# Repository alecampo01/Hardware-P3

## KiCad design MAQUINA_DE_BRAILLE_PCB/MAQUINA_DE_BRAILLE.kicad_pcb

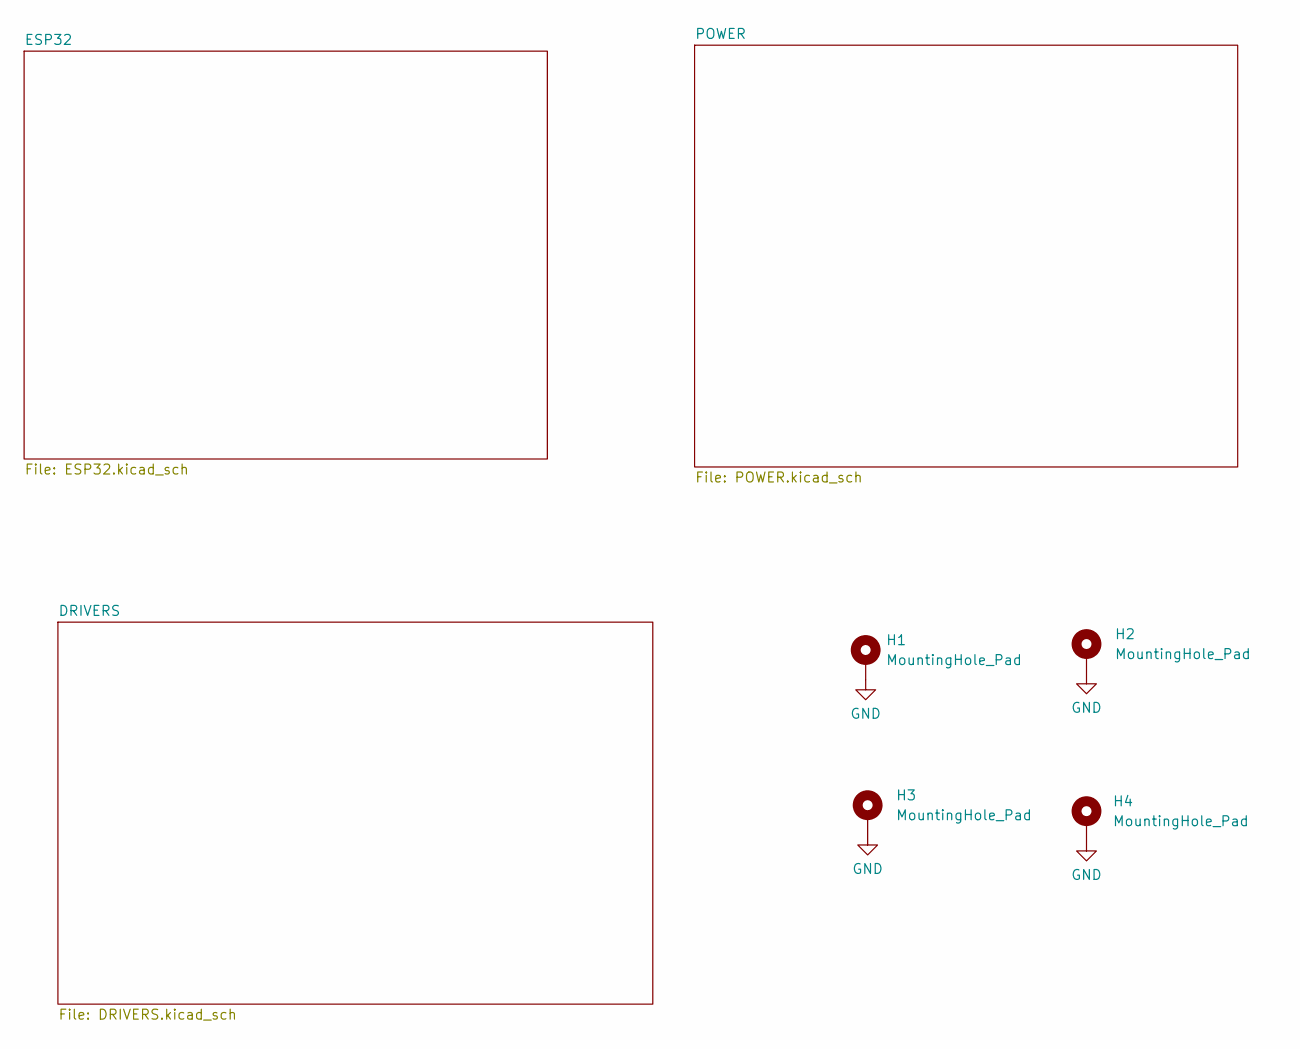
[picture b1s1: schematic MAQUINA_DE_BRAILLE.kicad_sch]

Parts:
H1, H2, H3, H4: MountingHole_Pad; MountingHole_3mm_Pad_Via

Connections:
GND: H1.1, H2.1, H3.1, H4.1; also elsewhere on the board

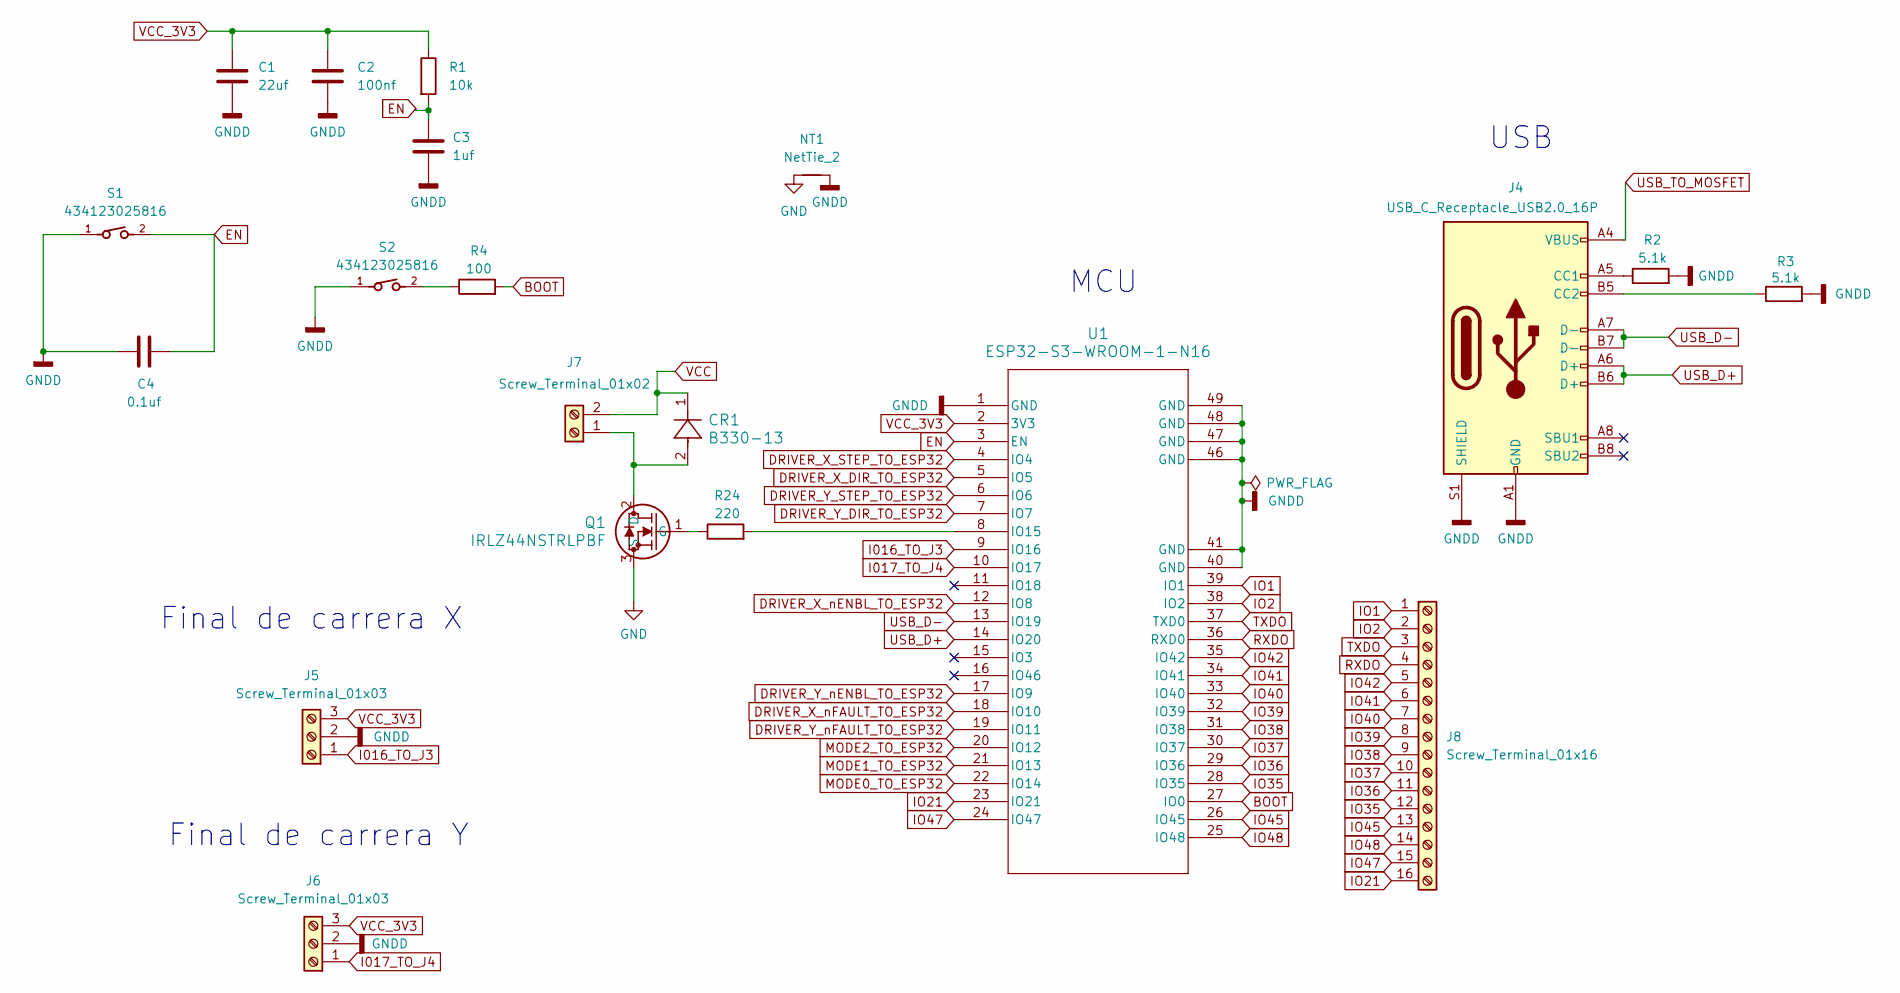
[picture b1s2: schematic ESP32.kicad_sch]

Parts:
C1: 22uf; C_0805_2012Metric_Pad1.18x1.45mm_HandSolder
C2: 100nf; C_0805_2012Metric_Pad1.18x1.45mm_HandSolder
C3: 1uf; C_0805_2012Metric_Pad1.18x1.45mm_HandSolder
C4: 0.1uf; C_0805_2012Metric_Pad1.18x1.45mm_HandSolder
CR1: B330-13; SMC_DIO
J4: USB_C_Receptacle_USB2.0_16P; USB_C_Receptacle_GCT_USB4105-xx-A_16P_TopMnt_Horizontal
J5, J6: Screw_Terminal_01x03; TerminalBlock_Xinya_XY308-2.54-3P_1x03_P2.54mm_Horizontal
J7: Screw_Terminal_01x02; TerminalBlock_Phoenix_MKDS-3-2-5.08_1x02_P5.08mm_Horizontal
J8: Screw_Terminal_01x16; TerminalBlock_Xinya_XY308-2.54-16P_1x16_P2.54mm_Horizontal
NT1: NetTie_2; NetTie-2_SMD_Pad2.0mm
Q1: IRLZ44NSTRLPBF; NMOSGDS_D2PAK_INF
R1: 10k; R_0805_2012Metric_Pad1.20x1.40mm_HandSolder
R2, R3: 5.1k; R_0805_2012Metric_Pad1.20x1.40mm_HandSolder
R4: 100; R_0805_2012Metric_Pad1.20x1.40mm_HandSolder
R24: 220; R_0805_2012Metric_Pad1.20x1.40mm_HandSolder
S1, S2: 434123025816
U1: ESP32-S3-WROOM-1-N16; ESP32-S3-WROOM-1_EXP

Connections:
BOOT: R4.2, U1.27 (IO0)
DRIVER_X_DIR_TO_ESP32: U1.5 (IO5); also elsewhere on the board
DRIVER_X_STEP_TO_ESP32: U1.4 (IO4); also elsewhere on the board
DRIVER_X_nENBL_TO_ESP32: U1.12 (IO8); also elsewhere on the board
DRIVER_X_nFAULT_TO_ESP32: U1.18 (IO10); also elsewhere on the board
DRIVER_Y_DIR_TO_ESP32: U1.7 (IO7); also elsewhere on the board
DRIVER_Y_STEP_TO_ESP32: U1.6 (IO6); also elsewhere on the board
DRIVER_Y_nENBL_TO_ESP32: U1.17 (IO9); also elsewhere on the board
DRIVER_Y_nFAULT_TO_ESP32: U1.19 (IO11); also elsewhere on the board
EN: C3.1, C4.2, R1.2, S1.2, U1.3 (EN); also elsewhere on the board
GND: NT1.1, Q1.3 (S); also elsewhere on the board
GNDD: C1.2, C2.2, C3.2, C4.1, J4.A1 (GND), J4.A12 (GND), J4.B1 (GND), J4.B12 (GND), J4.S1 (SHIELD), J5.2, J6.2, NT1.2, R2.2, R3.2, S1.1, S2.1, U1.1 (GND), U1.40 (GND), U1.41 (GND), U1.42, U1.43, U1.44, U1.45, U1.46 (GND), U1.47 (GND), U1.48 (GND), U1.49 (GND); also elsewhere on the board
I016_TO_J3: J5.1, U1.9 (IO16)
I017_TO_J4: J6.1, U1.10 (IO17)
IO1: J8.1, U1.39 (IO1)
IO2: J8.2, U1.38 (IO2)
IO21: J8.16, U1.23 (IO21)
IO35: J8.12, U1.28 (IO35)
IO36: J8.11, U1.29 (IO36)
IO37: J8.10, U1.30 (IO37)
IO38: J8.9, U1.31 (IO38)
IO39: J8.8, U1.32 (IO39)
IO40: J8.7, U1.33 (IO40)
IO41: J8.6, U1.34 (IO41)
IO42: J8.5, U1.35 (IO42)
IO45: J8.13, U1.26 (IO45)
IO47: J8.15, U1.24 (IO47)
IO48: J8.14, U1.25 (IO48)
MODE0_TO_ESP32: U1.22 (IO14); also elsewhere on the board
MODE1_TO_ESP32: U1.21 (IO13); also elsewhere on the board
MODE2_TO_ESP32: U1.20 (IO12); also elsewhere on the board
unnamed: J4.A5 (CC1), R2.1
unnamed: J4.B5 (CC2), R3.1
unnamed: CR1.2, J7.1, Q1.2 (D)
unnamed: Q1.1 (G), R24.1
unnamed 51: R4.1, S2.2; also elsewhere on the board
unnamed: R24.2, U1.8 (IO15)
RXDO: J8.4, U1.36 (RXD0)
TXDO: J8.3, U1.37 (TXD0)
USB_D+: J4.A6 (D+), J4.B6 (D+), U1.14 (IO20)
USB_D-: J4.A7 (D-), J4.B7 (D-), U1.13 (IO19)
USB_TO_MOSFET: J4.A4 (VBUS), J4.A9 (VBUS), J4.B4 (VBUS), J4.B9 (VBUS); also elsewhere on the board
VCC: CR1.1, J7.2; also elsewhere on the board
VCC_3V3: C1.1, C2.1, J5.3, J6.3, R1.1, U1.2 (3V3); also elsewhere on the board

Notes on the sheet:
USB
MCU
Final de carrera Y
Final de carrera X

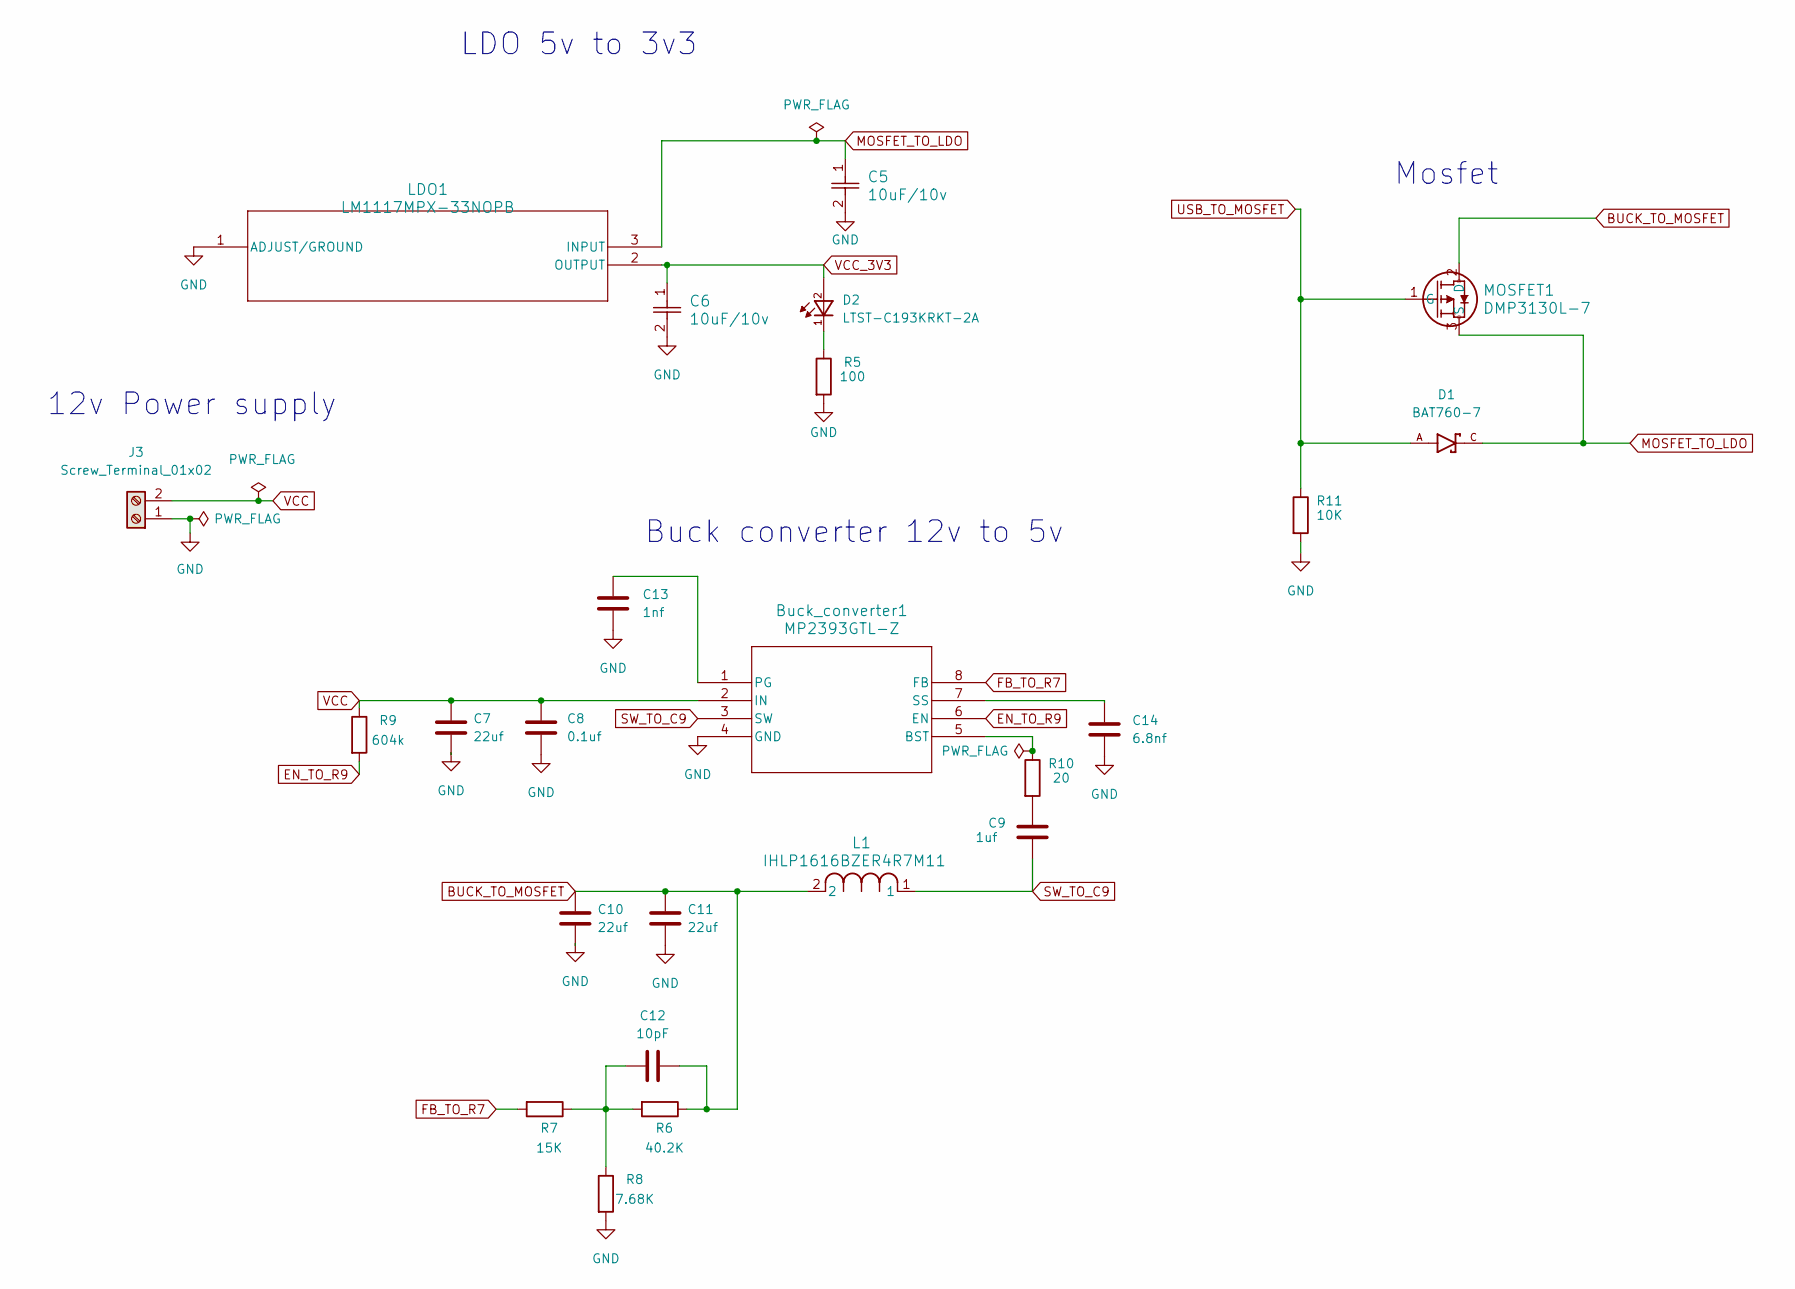
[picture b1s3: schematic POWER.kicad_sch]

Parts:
Buck_converter1: MP2393GTL-Z; SOT583_MP2393
C5, C6: 10uF/10v; CAP_293D_B_VIS
C7, C10, C11: 22uf; C_0805_2012Metric_Pad1.18x1.45mm_HandSolder
C8: 0.1uf; C_0805_2012Metric_Pad1.18x1.45mm_HandSolder
C9: 1uf; C_0805_2012Metric_Pad1.18x1.45mm_HandSolder
C12: 10pF; C_0805_2012Metric_Pad1.18x1.45mm_HandSolder
C13: 1nf; C_0805_2012Metric_Pad1.18x1.45mm_HandSolder
C14: 6.8nf; C_0805_2012Metric_Pad1.18x1.45mm_HandSolder
D1: BAT760-7; SOD2513X120N; PARTREV 9-2
D2: LTST-C193KRKT-2A; 0603
J3: Screw_Terminal_01x02; TerminalBlock_Phoenix_MKDS-3-2-5.08_1x02_P5.08mm_Horizontal
L1: IHLP1616BZER4R7M11; IND_IHLP-1616BZ_VIS
LDO1: LM1117MPX-33NOPB; SOT223-318H_OSI
MOSFET1: DMP3130L-7; SOT-23_DMP3130L_DIO
R5: 100; R_0805_2012Metric_Pad1.20x1.40mm_HandSolder
R6: 40.2K; R_0805_2012Metric_Pad1.20x1.40mm_HandSolder
R7: 15K; R_0805_2012Metric_Pad1.20x1.40mm_HandSolder
R8: 7.68K; R_0805_2012Metric_Pad1.20x1.40mm_HandSolder
R9: 604k; R_0805_2012Metric_Pad1.20x1.40mm_HandSolder
R10: 20; R_0805_2012Metric_Pad1.20x1.40mm_HandSolder
R11: 10K; R_0805_2012Metric_Pad1.20x1.40mm_HandSolder

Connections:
EN_TO_R9: Buck_converter1.6 (EN), R9.2
FB_TO_R7: Buck_converter1.8 (FB), R7.2
GND: Buck_converter1.4 (GND), C5.2, C6.2, C7.2, C8.2, C10.2, C11.2, C13.2, C14.2, J3.1, LDO1.1 (ADJUST/GROUND), R5.2, R8.2, R11.2; also elsewhere on the board
unnamed: Buck_converter1.5 (BST), R10.1
unnamed: Buck_converter1.1 (PG), C13.1
unnamed: Buck_converter1.7 (SS), C14.1
unnamed: C9.1, R10.2
unnamed: C12.1, R6.2, R7.1, R8.1
unnamed: D2.1, R5.1
SW_TO_C9: Buck_converter1.3 (SW), C9.2, L1.1
USB_TO_MOSFET: D1.A, MOSFET1.1 (G), R11.1; also elsewhere on the board
VCC: Buck_converter1.2 (IN), C7.1, C8.1, J3.2, R9.1; also elsewhere on the board
VCC_3V3: C6.1, D2.2, LDO1.2 (OUTPUT); also elsewhere on the board

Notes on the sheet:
Buck converter 12v to 5v
Mosfet
12v Power supply
LDO 5v to 3v3

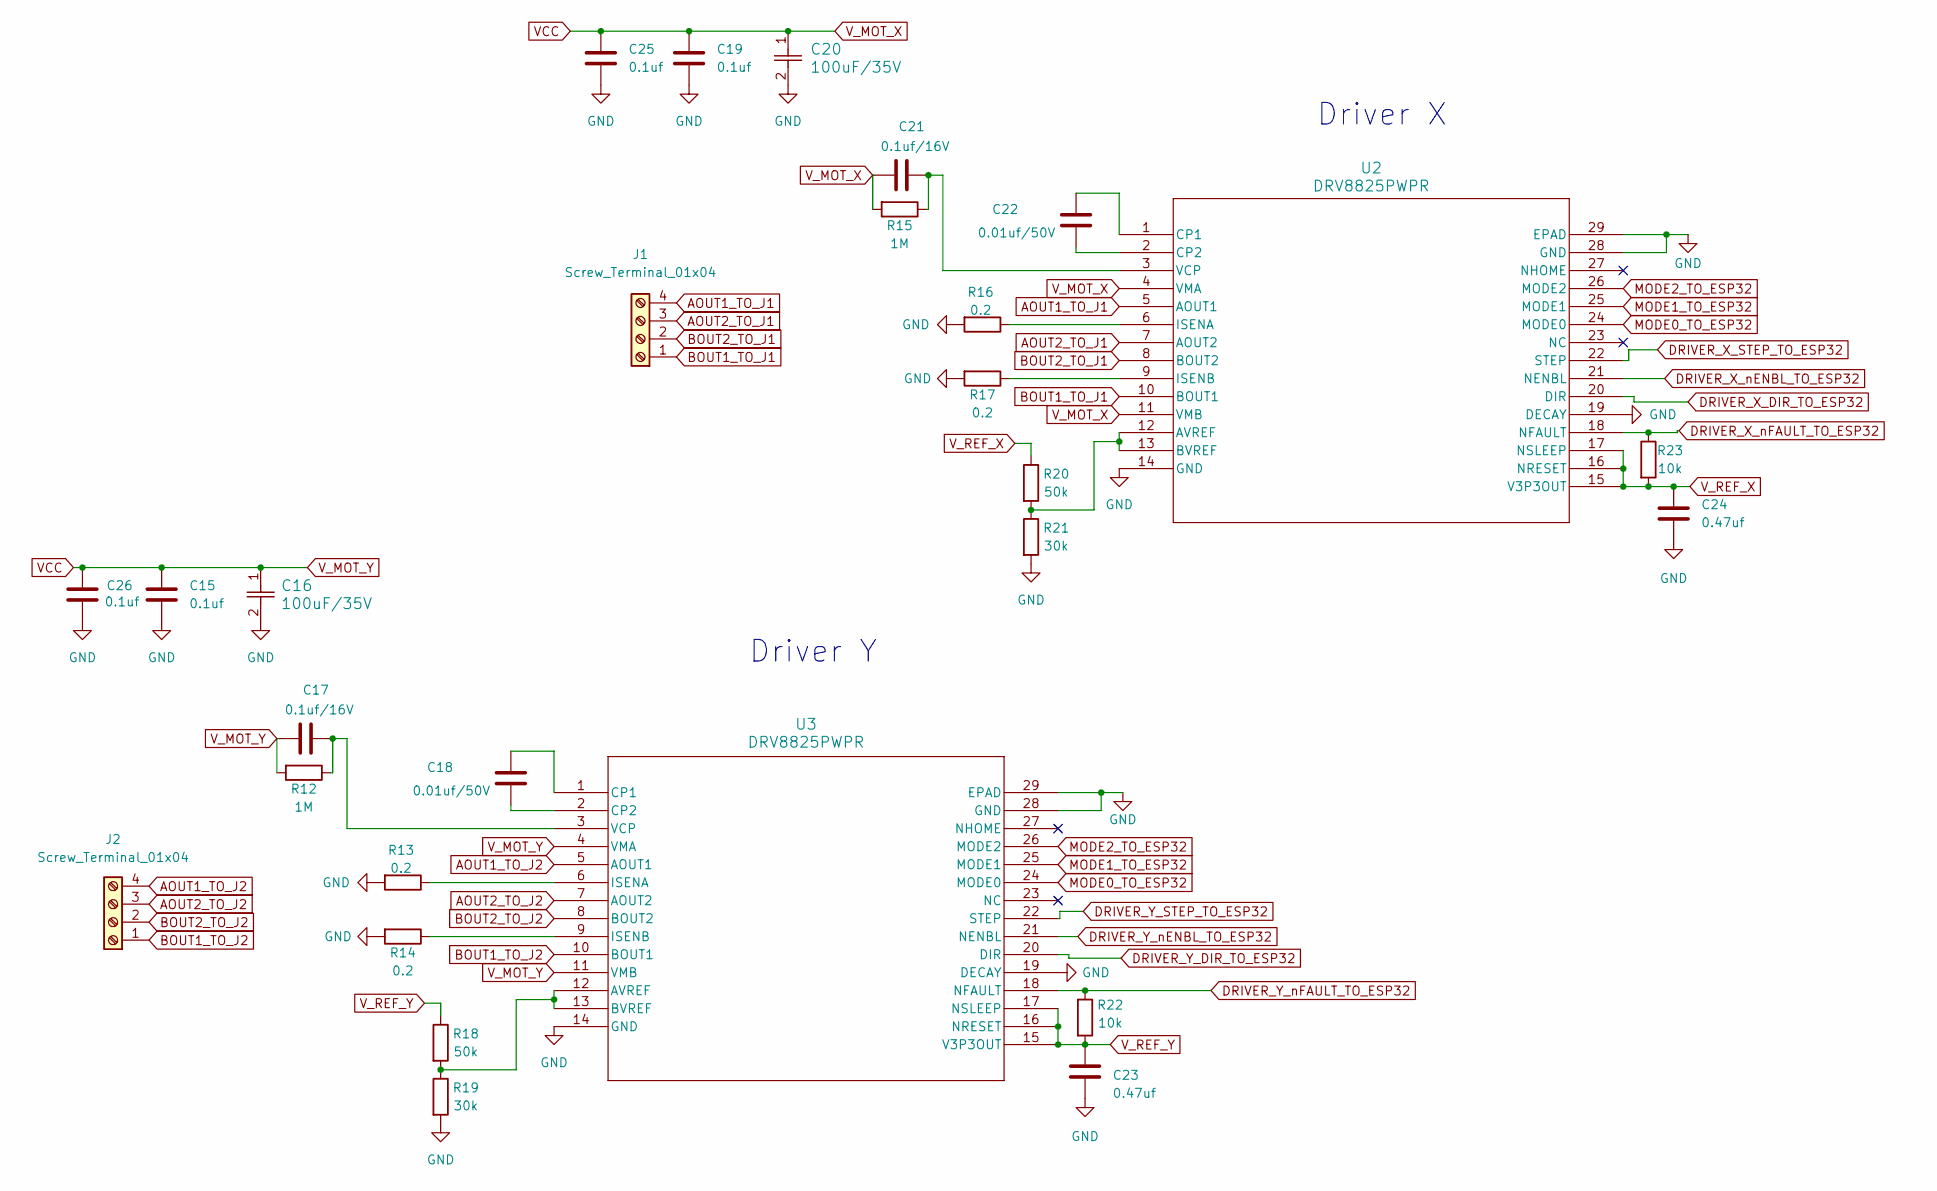
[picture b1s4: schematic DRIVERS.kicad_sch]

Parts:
C15, C19, C25, C26: 0.1uf; C_0805_2012Metric_Pad1.18x1.45mm_HandSolder
C16, C20: 100uF/35V; CAP_WCAP-ASLI_06p3X07p7_WRE
C17, C21: 0.1uf/16V; C_0805_2012Metric_Pad1.18x1.45mm_HandSolder
C18, C22: 0.01uf/50V; C_0805_2012Metric_Pad1.18x1.45mm_HandSolder
C23, C24: 0.47uf; C_0805_2012Metric_Pad1.18x1.45mm_HandSolder
J1, J2: Screw_Terminal_01x04; TerminalBlock_Xinya_XY308-2.54-4P_1x04_P2.54mm_Horizontal
R12, R15: 1M; R_0805_2012Metric_Pad1.20x1.40mm_HandSolder
R13, R14, R16, R17: 0.2; R_0805_2012Metric_Pad1.20x1.40mm_HandSolder
R18, R20: 50k; R_0805_2012Metric_Pad1.20x1.40mm_HandSolder
R19, R21: 30k; R_0805_2012Metric_Pad1.20x1.40mm_HandSolder
R22, R23: 10k; R_0805_2012Metric_Pad1.20x1.40mm_HandSolder
U2, U3: DRV8825PWPR; PWP28_5P18X3P1

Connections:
AOUT1_TO_J1: J1.4, U2.5 (AOUT1)
AOUT1_TO_J2: J2.4, U3.5 (AOUT1)
AOUT2_TO_J1: J1.3, U2.7 (AOUT2)
AOUT2_TO_J2: J2.3, U3.7 (AOUT2)
BOUT1_TO_J1: J1.1, U2.10 (BOUT1)
BOUT1_TO_J2: J2.1, U3.10 (BOUT1)
BOUT2_TO_J1: J1.2, U2.8 (BOUT2)
BOUT2_TO_J2: J2.2, U3.8 (BOUT2)
DRIVER_X_DIR_TO_ESP32: U2.20 (DIR); also elsewhere on the board
DRIVER_X_STEP_TO_ESP32: U2.22 (STEP); also elsewhere on the board
DRIVER_X_nENBL_TO_ESP32: U2.21 (NENBL); also elsewhere on the board
DRIVER_X_nFAULT_TO_ESP32: R23.1, U2.18 (NFAULT); also elsewhere on the board
DRIVER_Y_DIR_TO_ESP32: U3.20 (DIR); also elsewhere on the board
DRIVER_Y_STEP_TO_ESP32: U3.22 (STEP); also elsewhere on the board
DRIVER_Y_nENBL_TO_ESP32: U3.21 (NENBL); also elsewhere on the board
DRIVER_Y_nFAULT_TO_ESP32: R22.1, U3.18 (NFAULT); also elsewhere on the board
GND: C15.2, C16.2, C19.2, C20.2, C23.2, C24.2, C25.2, C26.2, R13.2, R14.2, R16.2, R17.2, R19.2, R21.2, U2.14 (GND), U2.19 (DECAY), U2.28 (GND), U2.29 (EPAD), U3.14 (GND), U3.19 (DECAY), U3.28 (GND), U3.29 (EPAD); also elsewhere on the board
MODE0_TO_ESP32: U2.24 (MODE0), U3.24 (MODE0); also elsewhere on the board
MODE1_TO_ESP32: U2.25 (MODE1), U3.25 (MODE1); also elsewhere on the board
MODE2_TO_ESP32: U2.26 (MODE2), U3.26 (MODE2); also elsewhere on the board
unnamed: R20.2, R21.1, U2.12 (AVREF), U2.13 (BVREF)
unnamed: C22.1, U2.1 (CP1)
unnamed: C22.2, U2.2 (CP2)
unnamed: R16.1, U2.6 (ISENA)
unnamed: R17.1, U2.9 (ISENB)
unnamed: C21.1, R15.1, U2.3 (VCP)
unnamed: R18.2, R19.1, U3.12 (AVREF), U3.13 (BVREF)
unnamed: C18.1, U3.1 (CP1)
unnamed: C18.2, U3.2 (CP2)
unnamed: R13.1, U3.6 (ISENA)
unnamed: R14.1, U3.9 (ISENB)
unnamed: C17.1, R12.1, U3.3 (VCP)
VCC: C15.1, C16.1, C17.2, C19.1, C20.1, C21.2, C25.1, C26.1, R12.2, R15.2, U2.4 (VMA), U2.11 (VMB), U3.4 (VMA), U3.11 (VMB); also elsewhere on the board
V_REF_X: C24.1, R20.1, R23.2, U2.15 (V3P3OUT), U2.16 (NRESET), U2.17 (NSLEEP)
V_REF_Y: C23.1, R18.1, R22.2, U3.15 (V3P3OUT), U3.16 (NRESET), U3.17 (NSLEEP)

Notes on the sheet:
Driver Y
Driver X

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
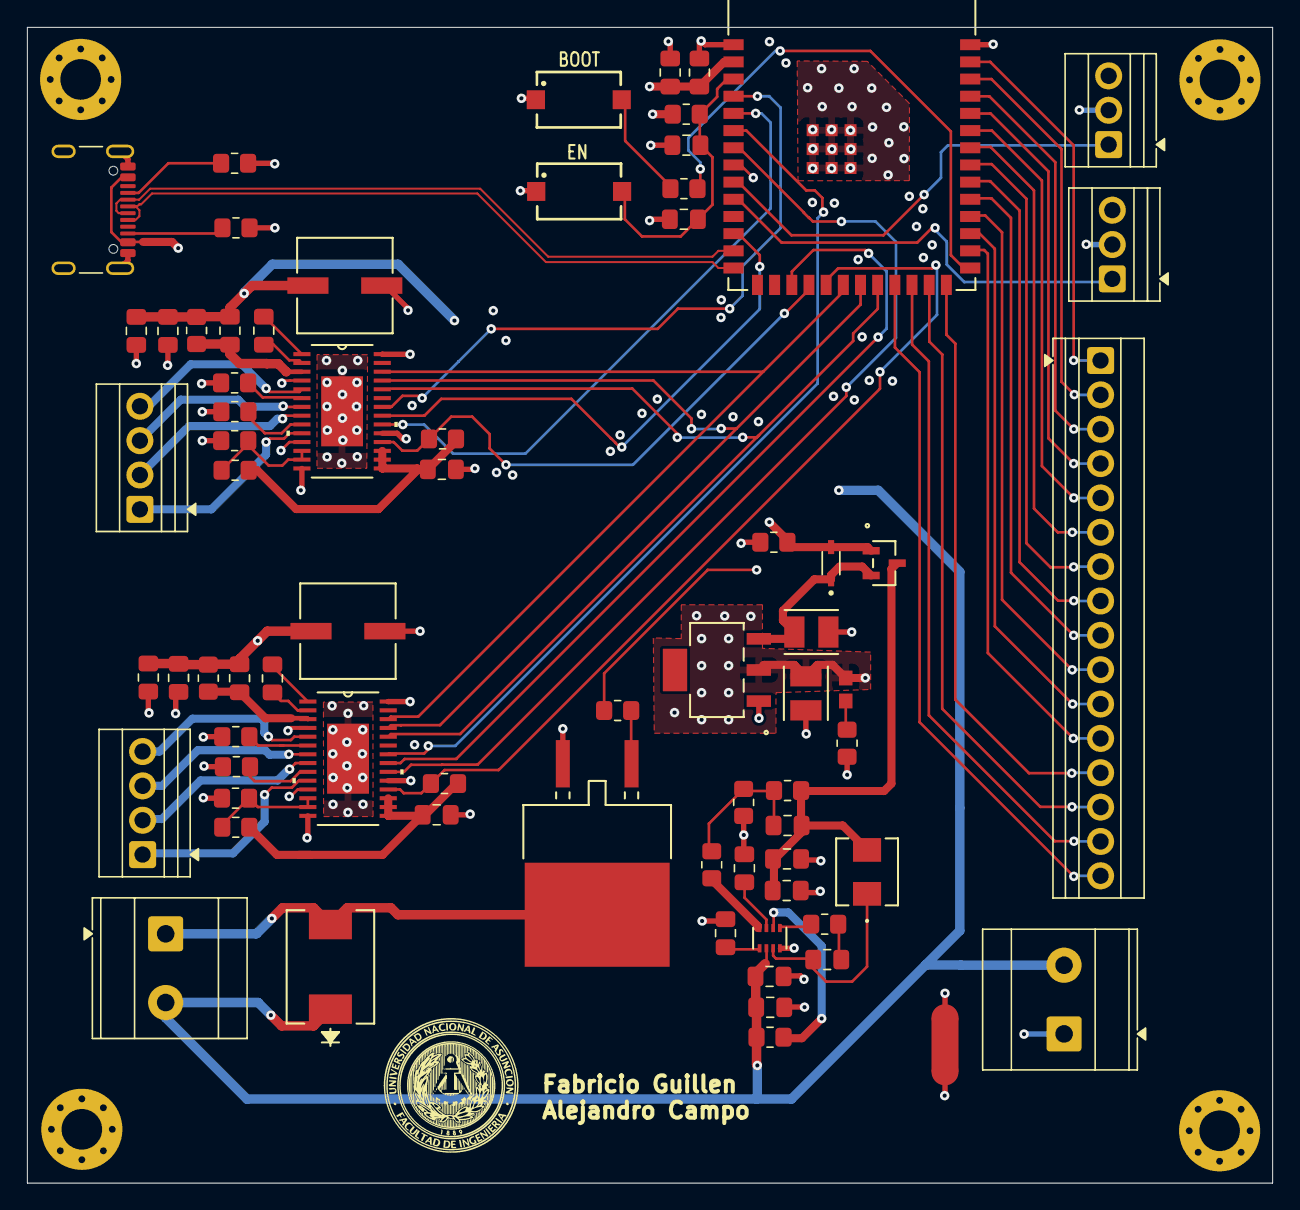
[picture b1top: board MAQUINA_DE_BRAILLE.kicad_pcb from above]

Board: 4 copper layers, 92.1 x 85.4 mm, 76 parts (0 on the bottom side), 77 nets.

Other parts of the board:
BOOT: 434123025816
EN: 434123025816

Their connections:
EN: EN.2; also elsewhere on the board
GNDD: BOOT.1, EN.1; also elsewhere on the board
unnamed 51: BOOT.2; also elsewhere on the board

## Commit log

2026-03-28 Primer proyecto
2026-03-28 tuki
2026-03-29 last update
2026-03-29 fabri puto
2026-03-29 ListaDeCompras.xlsx
2026-03-29 carga de la lista
